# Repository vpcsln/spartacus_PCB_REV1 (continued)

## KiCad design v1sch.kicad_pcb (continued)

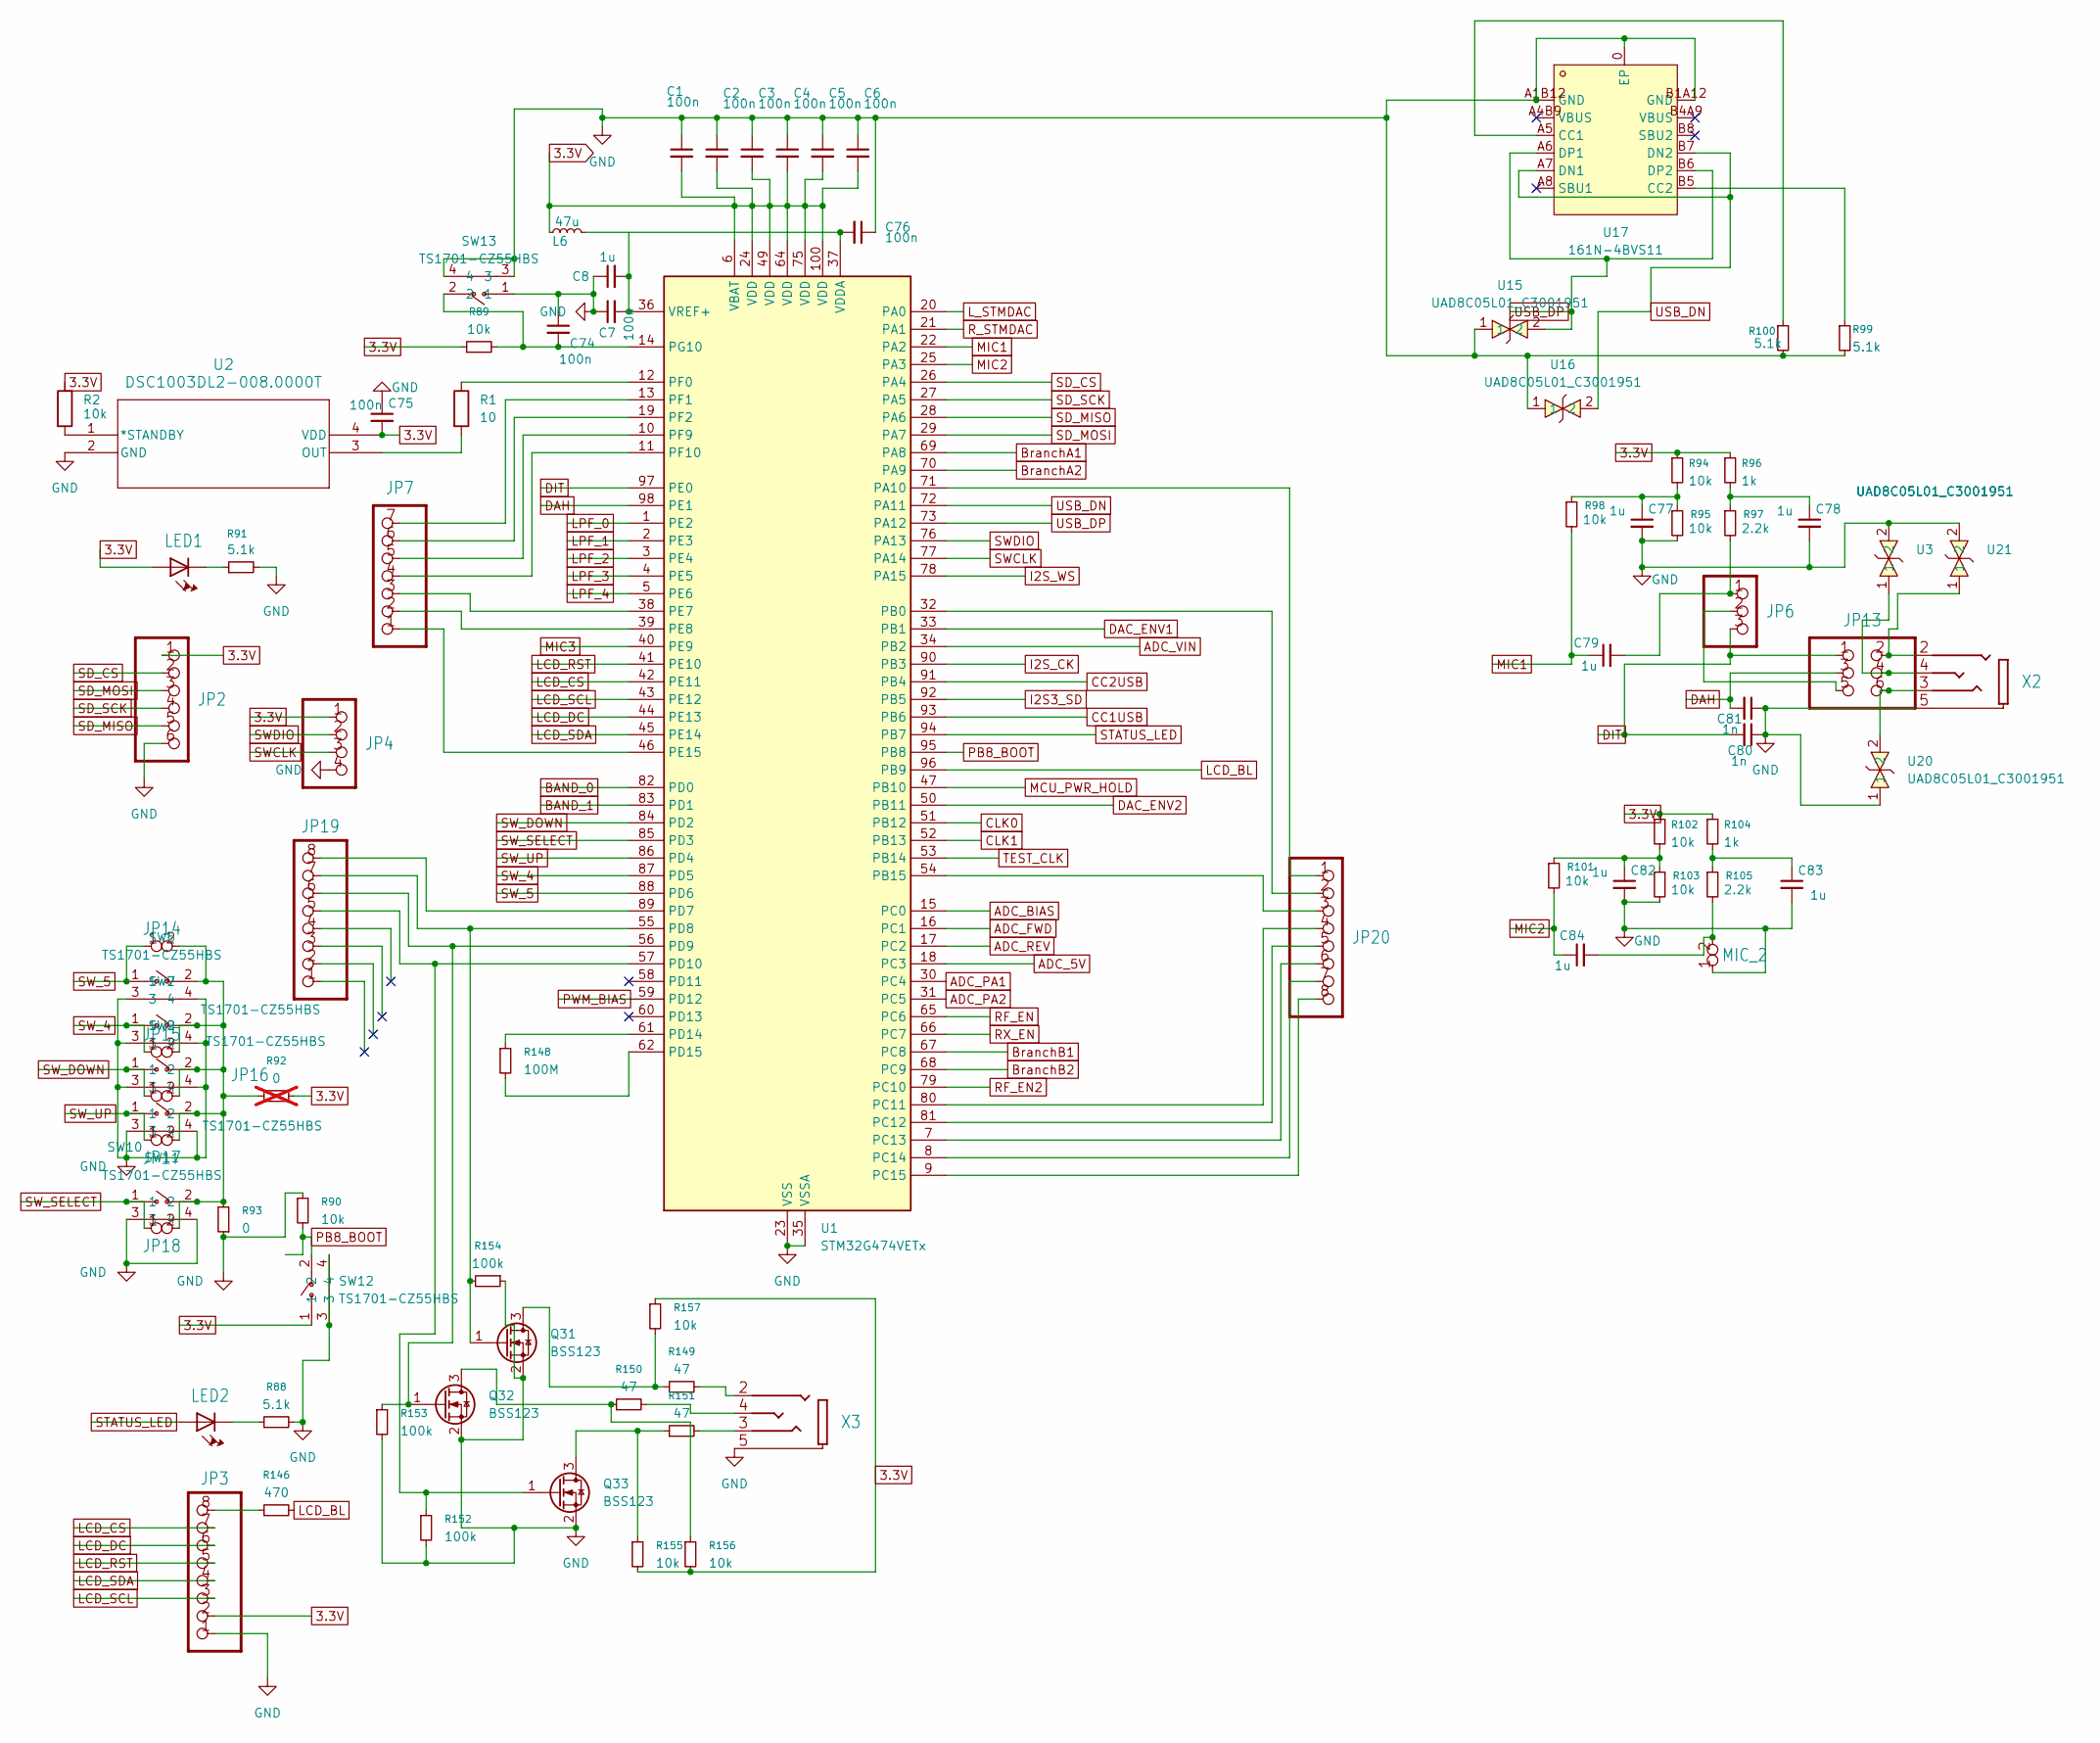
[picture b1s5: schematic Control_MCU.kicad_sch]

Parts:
C1, C2, C3, C4, C5, C6, C7, C74, C75, C76: 100n; C_1206_3216Metric_Pad1.33x1.80mm_HandSolder
C8, C77, C78, C79, C82, C83, C84: 1u; C_1206_3216Metric_Pad1.33x1.80mm_HandSolder
C80, C81: 1n; C_1206_3216Metric_Pad1.33x1.80mm_HandSolder
JP2: 1X06
JP3: 1X08
JP4: 1X04
JP6: 1X03
JP7: 1X07
JP13: 2X03
JP14, JP15, JP16, JP17, JP18: 1X02
JP19, JP20: 1X08-BIG
L6: 47u; L_Axial_L9.5mm_D4.0mm_P2.54mm_Vertical_Fastron_SMCC
LED1, LED2: HLMP-1790
MIC_2: 1X02
Q31, Q32, Q33: BSS123; SOT-23
R1: 10; R_1206_3216Metric_Pad1.30x1.75mm_HandSolder
R2, R89, R90, R94, R95, R98, R101, R102, R103, R155, R156, R157: 10k; R_1206_3216Metric_Pad1.30x1.75mm_HandSolder
R88, R91, R99, R100: 5.1k; R_1206_3216Metric_Pad1.30x1.75mm_HandSolder
R92: 0; R_1206_3216Metric_Pad1.30x1.75mm_HandSolder; not fitted
R93: 0; R_1206_3216Metric_Pad1.30x1.75mm_HandSolder
R96, R104: 1k; R_1206_3216Metric_Pad1.30x1.75mm_HandSolder
R97, R105: 2.2k; R_1206_3216Metric_Pad1.30x1.75mm_HandSolder
R146: 470; R_1206_3216Metric_Pad1.30x1.75mm_HandSolder
R148: 100M; R_01005_0402Metric
R149, R150, R151: 47; R_1206_3216Metric_Pad1.30x1.75mm_HandSolder
R152, R153, R154: 100k; R_1206_3216Metric_Pad1.30x1.75mm_HandSolder
SW6, SW7, SW9, SW10, SW11, SW12, SW13: TS1701-CZ55HBS; SW-TH_4P-L7.5-W5.5-P4.50; MPN TS1701-CZ55HBS; LCSC Part C36938820
U1: STM32G474VETx; LQFP-100_14x14mm_P0.5mm
U2: DSC1003DL2-008.0000T; CDFN-4_2x2.5mm_P1.65mm
U3, U15, U16, U20, U21: UAD8C05L01_C3001951; SOD-882_L1.0-W0.6-BI; MPN UAD8C05L01(UMW); LCSC Part C3001951
U17: 161N-4BVS11; USB-C-SMD_HANELECTRICITY_161N-4XVS11; MPN 161N-4BVS11; LCSC Part C5440752
X2, X3: PJ320A

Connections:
3.3V: C1.2, C2.2, C3.2, C4.2, C5.2, C6.2, C75.2, JP2.1, JP3.2, JP4.1, L6.1, LED1.A, R2.1, R89.1, R92.2, R94.1, R96.1, R102.1, R104.1, R155.2, R156.2, R157.1, SW12.1, U1.6 (VBAT), U1.24 (VDD), U1.49 (VDD), U1.64 (VDD), U1.75 (VDD), U1.100 (VDD), U2.4 (VDD); also elsewhere on the board
ADC_5V: U1.18 (PC3); also elsewhere on the board
ADC_BIAS: U1.15 (PC0); also elsewhere on the board
ADC_FWD: U1.16 (PC1); also elsewhere on the board
ADC_PA1: U1.30 (PC4); also elsewhere on the board
ADC_PA2: U1.31 (PC5); also elsewhere on the board
ADC_REV: U1.17 (PC2); also elsewhere on the board
ADC_VIN: U1.34 (PB2); also elsewhere on the board
BAND_0: U1.82 (PD0); also elsewhere on the board
BAND_1: U1.83 (PD1); also elsewhere on the board
BranchA1: U1.69 (PA8); also elsewhere on the board
BranchA2: U1.70 (PA9); also elsewhere on the board
BranchB1: U1.67 (PC8); also elsewhere on the board
BranchB2: U1.68 (PC9); also elsewhere on the board
CC1USB: U1.93 (PB6); also elsewhere on the board
CC2USB: U1.91 (PB4); also elsewhere on the board
CLK0: U1.51 (PB12); also elsewhere on the board
CLK1: U1.52 (PB13); also elsewhere on the board
DAC_ENV1: U1.33 (PB1); also elsewhere on the board
DAC_ENV2: U1.50 (PB11); also elsewhere on the board
DAH: C81.2, JP13.3, U1.98 (PE1)
DIT: C80.2, JP6.3, JP13.1, U1.97 (PE0)
GND: C1.1, C2.1, C3.1, C4.1, C5.1, C6.1, C7.1, C8.1, C74.1, C75.1, C76.1, C77.2, C78.2, C80.1, C81.1, C82.2, C83.2, JP2.6, JP3.1, JP4.4, MIC_2.1, Q31.2 (S), Q32.2 (S), Q33.2 (S), R88.2, R90.1, R91.2, R93.1, R95.2, R99.2, R100.2, R103.2, R152.2, R153.2, R154.1, SW6.3, SW6.4, SW7.3, SW7.4, SW9.3, SW9.4, SW10.3, SW10.4, SW11.3, SW11.4, SW12.3, SW12.4, SW13.1, SW13.3, SW13.4, U1.23 (VSS), U1.35 (VSSA), U1.48 (VSS), U1.63 (VSS), U1.74 (VSS), U1.99 (VSS), U2.2 (GND), U3.2, U15.1, U16.1, U17.0 (EP), U17.A1B12 (GND), U17.B1A12 (GND), U20.1, U21.2, X2.5, X3.5; also elsewhere on the board
I2S3_SD: U1.92 (PB5); also elsewhere on the board
I2S_CK: U1.90 (PB3); also elsewhere on the board
I2S_WS: U1.78 (PA15); also elsewhere on the board
LCD_BL: R146.2, U1.96 (PB9)
LCD_CS: JP3.7, U1.42 (PE11)
LCD_DC: JP3.6, U1.44 (PE13)
LCD_RST: JP3.5, U1.41 (PE10)
LCD_SCL: JP3.3, U1.43 (PE12)
LCD_SDA: JP3.4, U1.45 (PE14)
LPF_0: U1.1 (PE2); also elsewhere on the board
LPF_1: U1.2 (PE3); also elsewhere on the board
LPF_2: U1.3 (PE4); also elsewhere on the board
LPF_3: U1.4 (PE5); also elsewhere on the board
LPF_4: U1.5 (PE6); also elsewhere on the board
L_STMDAC: U1.20 (PA0); also elsewhere on the board
MCU_PWR_HOLD: U1.47 (PB10); also elsewhere on the board
MIC1: C79.1, R98.2, U1.22 (PA2)
MIC2: C84.1, R101.2, U1.25 (PA3)
MIC3: U1.40 (PE9); also elsewhere on the board
unnamed: C77.1, R94.2, R95.1, R98.1
unnamed: C78.1, R96.2, R97.1
unnamed: C79.2, JP6.1, R97.2
unnamed: C82.1, R101.1, R102.2, R103.1
unnamed: C83.1, R104.2, R105.1
unnamed: C84.2, MIC_2.2, R105.2
unnamed: JP3.8, R146.1
unnamed: JP13.2, U21.1, X2.2
unnamed: JP13.4, U3.1, X2.4
unnamed: JP6.2, JP13.5
unnamed: JP13.6, U20.2, X2.3
unnamed: JP14.2, JP15.2, JP16.2, JP17.2, JP18.2, R92.1, R93.2, SW6.2, SW7.2, SW9.2, SW10.2, SW11.2
unnamed: LED1.C, R91.1
unnamed: LED2.C, R88.1
unnamed: Q31.3 (D), R149.1, R157.2
unnamed: JP19.7, Q31.1 (G), R154.2, U1.55 (PD8)
unnamed: Q32.3 (D), R150.1, R156.1
unnamed: JP19.6, Q32.1 (G), R153.1, U1.56 (PD9)
unnamed: Q33.3 (D), R151.1, R155.1
unnamed: JP19.5, Q33.1 (G), R152.1, U1.57 (PD10)
unnamed: R149.2, X3.2
unnamed: R150.2, X3.4
unnamed: R151.2, X3.3
unnamed: JP20.1, U1.71 (PA10)
unnamed: JP20.2, U1.32 (PB0)
unnamed: JP20.3, U1.54 (PB15)
unnamed: JP20.4, U1.80 (PC11)
unnamed: JP20.5, U1.81 (PC12)
unnamed: JP20.6, U1.7 (PC13)
unnamed: JP20.7, U1.8 (PC14)
unnamed: JP20.8, U1.9 (PC15)
unnamed: JP19.8, U1.89 (PD7)
unnamed: R148.1, U1.61 (PD14)
unnamed: R148.2, U1.62 (PD15)
unnamed: JP7.3, U1.38 (PE7)
unnamed: JP7.2, U1.39 (PE8)
unnamed: JP7.1, U1.46 (PE15)
unnamed: R1.1, U1.12 (PF0)
unnamed: JP7.7, U1.13 (PF1)
unnamed: JP7.6, U1.19 (PF2)
unnamed: JP7.5, U1.10 (PF9)
unnamed: JP7.4, U1.11 (PF10)
unnamed: C74.2, R89.2, SW13.2, U1.14 (PG10)
unnamed: C76.2, L6.2, U1.37 (VDDA)
unnamed: C7.2, C8.2, U1.36 (VREF+)
unnamed: R2.2, U2.1 (*STANDBY)
unnamed: R1.2, U2.3 (OUT)
unnamed: R100.1, U17.A5 (CC1)
unnamed: R99.1, U17.B5 (CC2)
PB8_BOOT: R90.2, SW12.2, U1.95 (PB8)
PWM_BIAS: U1.59 (PD12); also elsewhere on the board
RF_EN: U1.65 (PC6); also elsewhere on the board
RF_EN2: U1.79 (PC10); also elsewhere on the board
RX_EN: U1.66 (PC7); also elsewhere on the board
R_STMDAC: U1.21 (PA1); also elsewhere on the board
SD_CS: JP2.2, U1.26 (PA4)
SD_MISO: JP2.5, U1.28 (PA6)
SD_MOSI: JP2.3, U1.29 (PA7)
SD_SCK: JP2.4, U1.27 (PA5)
STATUS_LED: LED2.A, U1.94 (PB7)
SWCLK: JP4.3, U1.77 (PA14)
SWDIO: JP4.2, U1.76 (PA13)
SW_4: JP15.1, SW7.1, U1.87 (PD5)
SW_5: JP14.1, SW6.1, U1.88 (PD6)
SW_DOWN: JP16.1, SW9.1, U1.84 (PD2)
SW_SELECT: JP18.1, SW11.1, U1.85 (PD3)
SW_UP: JP17.1, SW10.1, U1.86 (PD4)
TEST_CLK: U1.53 (PB14); also elsewhere on the board
USB_DN: U1.72 (PA11), U16.2, U17.A7 (DN1), U17.B7 (DN2)
USB_DP: U1.73 (PA12), U15.2, U17.A6 (DP1), U17.B6 (DP2)

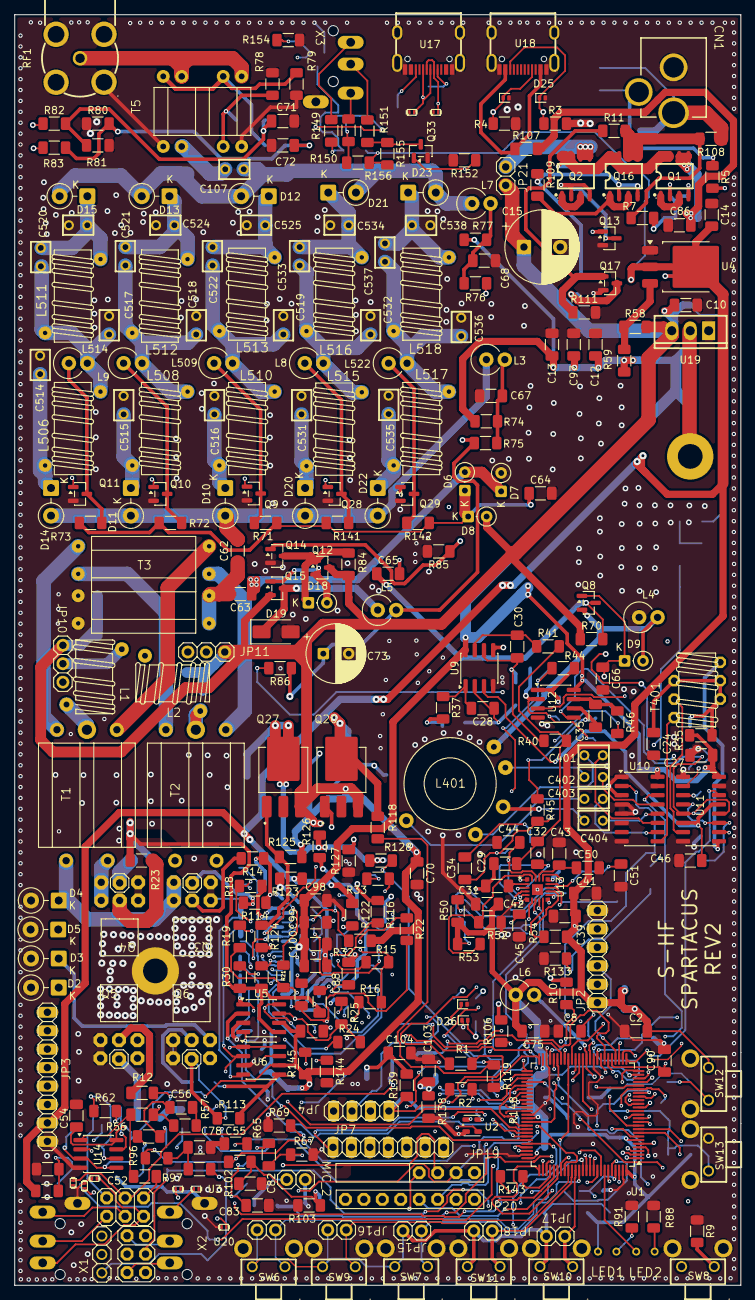
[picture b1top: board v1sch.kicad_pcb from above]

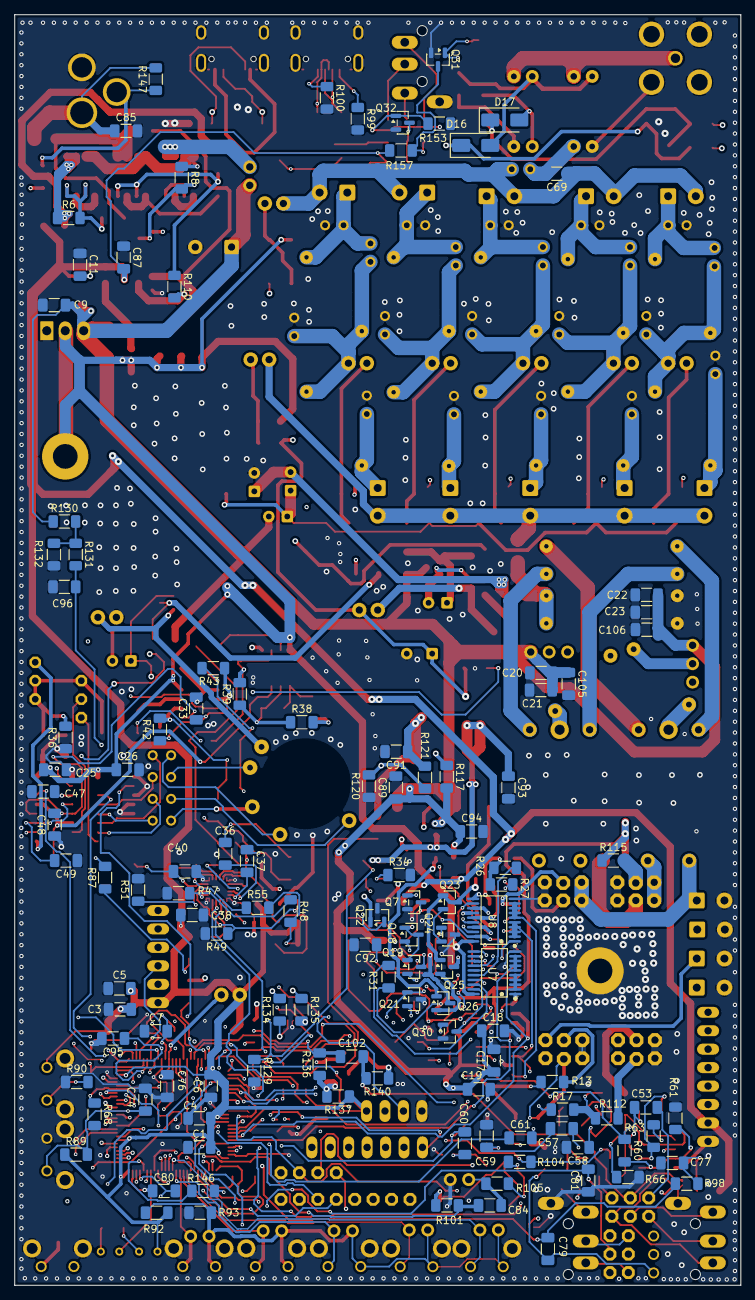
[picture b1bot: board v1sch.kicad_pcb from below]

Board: 6 copper layers, 100.0 x 175.0 mm, 436 parts (120 on the bottom side), 292 nets.
